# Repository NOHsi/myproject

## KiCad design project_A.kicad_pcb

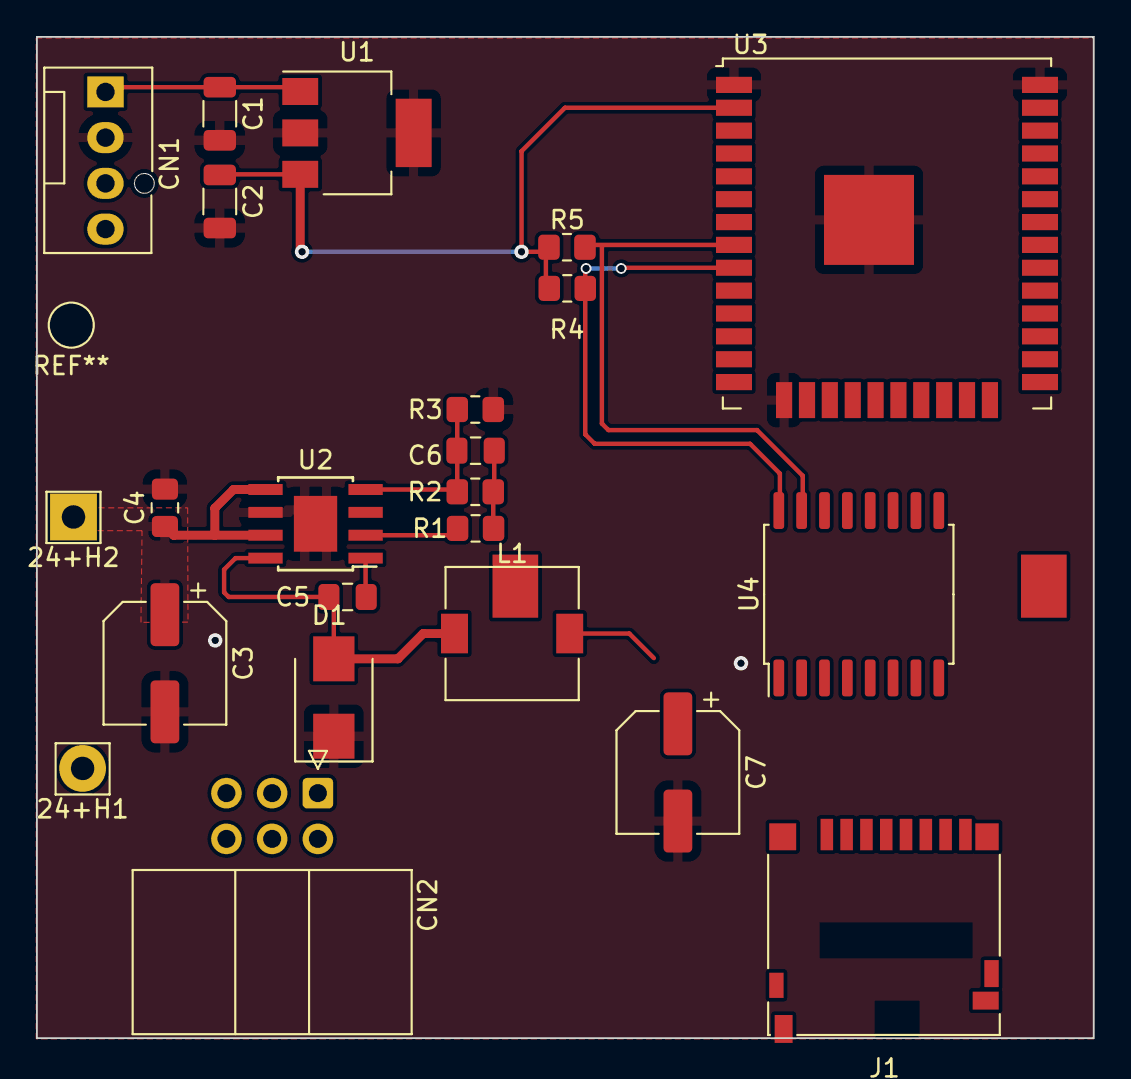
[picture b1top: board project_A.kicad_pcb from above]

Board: 2 copper layers, 58.7 x 55.6 mm, 24 parts (1 on the bottom side), 13 nets.

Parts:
24+H1, 24+H2: MountingHole; Pin_D1.3mm_L11.3mm_W2.8mm_Flat
BT1: Battery_Cell; BatteryHolder_Keystone_1058_1x2032
C1, C2: C104; C_1206_3216Metric
C3: 10uF/50V(C3216); CP_Elec_6.3x4.5
C4, C5, C6: C104; C_0805_2012Metric_Pad1.18x1.45mm_HandSolder
C7: 100uF/50V; CP_Elec_6.3x4.5
CN1: Conn_01x04; FanPinHeader_1x04_P2.54mm_Vertical
CN2: Conn_01x04; IDC-Header_2x03_P2.54mm_Horizontal
D1: STPS3L60U; D_SMB
J1: SD_Card; microSD_HC_Hirose_DM3D-SF
L1: 10uH(YCDM6045T); L_7.3x7.3_H4.5
R1: 47K(R1608); R_0805_2012Metric_Pad1.20x1.40mm_HandSolder
R2, R3: 187K(R1608); R_0805_2012Metric_Pad1.20x1.40mm_HandSolder
R4, R5: 1K; R_0805_2012Metric_Pad1.20x1.40mm_HandSolder
U1: LT1129-3.3_SOT223; SOT-223-3_TabPin2
U2: ST1S14PHR; TI_SO-PowerPAD-8
U3: ESP32-WROOM-32U
U4: DS3231M; SOIC-16W_7.5x10.3mm_P1.27mm

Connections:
+3.3V: C2.1, R4.2, R5.2, U1.3 (VO), U3.2 (VDD)
+5V: C1.1, CN1.1, U1.1 (VI)
+24V: C3.1, C4.1, U2.5 (EN2), U2.7 (VIN)
/+5V OUT: C7.1, L1.2
GND: C1.2, C2.2, C3.2, C4.2, C7.2, CN1.2, D1.1 (K), R3.1, U1.2 (GND), U2.6 (GND), U2.9 (PADGND), U3.1 (GND), U3.15 (GND), U3.38 (GND), U3.39 (GND)
unnamed: C5.1, U2.1 (BOOT)
unnamed: C5.2, D1.2 (A), L1.1, U2.8 (SW)
unnamed: C6.1, R2.1, R3.2, U2.4 (FB)
unnamed: C6.2, R1.2, R2.2
unnamed: R1.1, U2.2 (PG)
unnamed: U4.5 (GND), U4.6 (GND), U4.7 (GND), U4.8 (GND), U4.9 (GND), U4.10 (GND), U4.11 (GND), U4.12 (GND), U4.13 (GND)
SCL: R4.1, U3.9 (IO33), U4.16 (SCL)
SDA: R5.1, U3.8 (IO32), U4.15 (SDA)

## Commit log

2022-08-03 add first kicad_sch
2022-08-03 modefied file kicad_sch
2022-08-04 add .svg
2022-08-04 add .svg - test
2022-08-04 add .svg - test --test
2022-11-11 feat : 기능추가
2022-11-11 feat : test
